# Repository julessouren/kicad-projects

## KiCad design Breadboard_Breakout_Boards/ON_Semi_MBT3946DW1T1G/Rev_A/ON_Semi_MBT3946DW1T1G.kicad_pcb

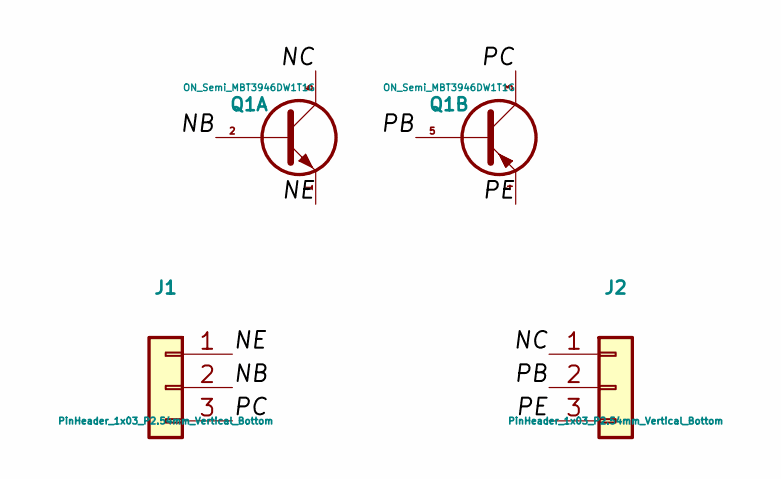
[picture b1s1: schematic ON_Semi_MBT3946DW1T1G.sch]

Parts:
J1, J2: PinHeader_1x03_P2.54mm_Vertical_Bottom
Q1: ON_Semi_MBT3946DW1T1G; ON_Semi_MBT3946DW1T1G_SOT-363_SC-70-6_SC-80

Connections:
/NB: J1.2, Q1.2 (B1)
/NC: J2.1, Q1.6 (C1)
/NE: J1.1, Q1.1 (E1)
/PB: J2.2, Q1.5 (B2)
/PC: J1.3, Q1.3 (C2)
/PE: J2.3, Q1.4 (E2)

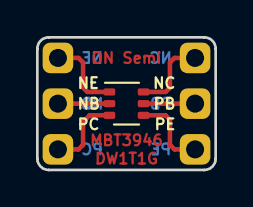
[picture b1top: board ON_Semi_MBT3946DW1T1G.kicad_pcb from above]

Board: 2 copper layers, 9.9 x 7.4 mm, 3 parts (0 on the bottom side), 6 nets.

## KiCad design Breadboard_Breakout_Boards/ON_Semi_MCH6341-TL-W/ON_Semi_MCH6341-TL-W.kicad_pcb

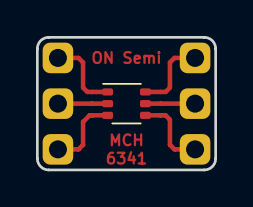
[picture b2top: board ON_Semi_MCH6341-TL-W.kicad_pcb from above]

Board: 2 copper layers, 9.9 x 7.4 mm, 3 parts (0 on the bottom side), 3 nets.

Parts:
J1, J2: PinHeader_1x03_P2.54mm_Vertical_Bottom
Q1: ON_Semi_MCH6341-TL-W; ON_Semi_MCH6341-TL-W_SOT-363_SC-70-6_SC-88

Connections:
/D: J1.1, J1.2, J2.1, J2.2, Q1.D
/G: J1.3, Q1.G
/S: J2.3, Q1.S

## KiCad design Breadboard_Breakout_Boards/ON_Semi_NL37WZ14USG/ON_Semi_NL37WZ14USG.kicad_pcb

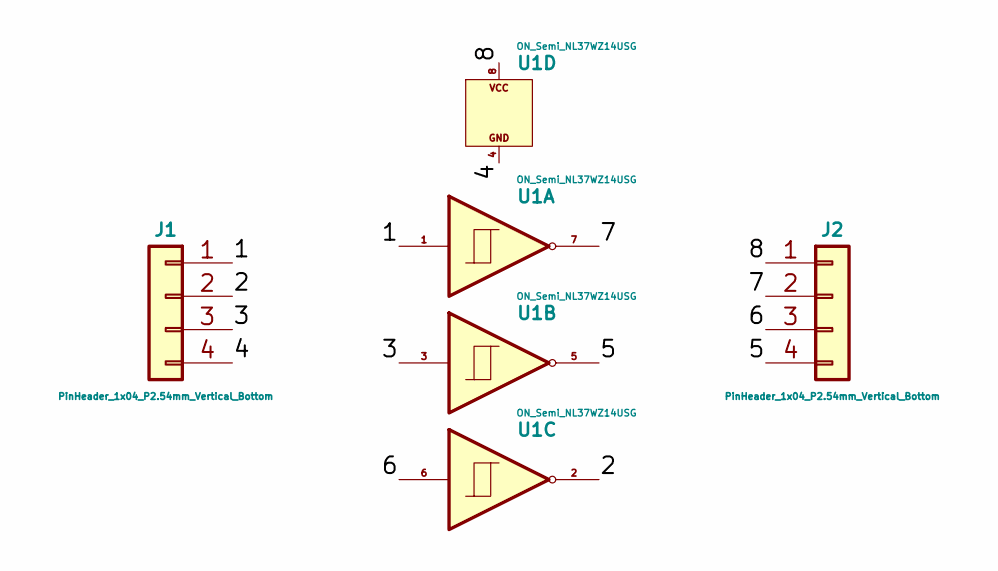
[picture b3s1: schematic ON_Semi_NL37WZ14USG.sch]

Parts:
J1, J2: PinHeader_1x04_P2.54mm_Vertical_Bottom
U1: ON_Semi_NL37WZ14USG; ON_Semi_NL37WZ14USG_US8-8

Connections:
/1: J1.1, U1.1
/2: J1.2, U1.2
/3: J1.3, U1.3
/4: J1.4, U1.4
/5: J2.4, U1.5
/6: J2.3, U1.6
/7: J2.2, U1.7
/8: J2.1, U1.8

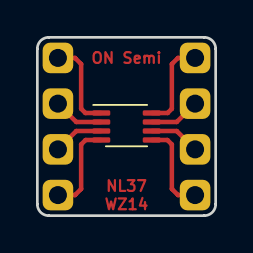
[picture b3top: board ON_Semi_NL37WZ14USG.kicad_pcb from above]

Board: 2 copper layers, 9.9 x 9.9 mm, 3 parts (0 on the bottom side), 8 nets.
